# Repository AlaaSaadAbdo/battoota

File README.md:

# Disclaimer: Please keep in mind that there are prototypes here. Use the files at your own risk.

# Pictures

## Credits/references

All of the boards here wouldn't be possible without the help of some awesome people and their projects:
- [bredfield](https://github.com/bredfield)
- [Rae Dux](https://github.com/andrewjrae/rae-dux)
- [Rufous/Berylline](https://github.com/jcmkk3/trochilidae)
- [Sadek Baroudi](https://github.com/sadekbaroudi) of [fingerpunch](https://fingerpunch.xyz)
- [Hazel](https://github.com/jasonhazel)
- [Freznel](https://github.com/freznel10)
- [Duckyb](https://github.com/duckyb)
- [Grinnie](https://github.com/regicidalplutophage)
- [Weteor](https://github.com/weteor)
- [aki27](https://twitter.com/aki27kbd)
- [chewiedies](https://www.printables.com/@chewiedies_360738)

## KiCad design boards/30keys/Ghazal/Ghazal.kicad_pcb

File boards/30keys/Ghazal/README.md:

Ghazal is a wireless unibody.

Features:
- Integrated trackball using the PWM3610 via [VIK module](https://github.com/sadekbaroudi/vik/tree/master/pcb/pmw3610-xs)
- Display using nice!view
- Wireless using nice!nano

To build this board you'll need the following components after fabrication the board with PCBA

BOM:
- 1x nice!nano 
- 1x nice!view
- 1x battery I recommend a chunky one similar to LP785060
- XS-PMW3610 VIK module PCBA
- 34 MX/ChocV1 hotswap sockets
- 34 MX/CHocV1 switches
- Keycaps for the chose switches

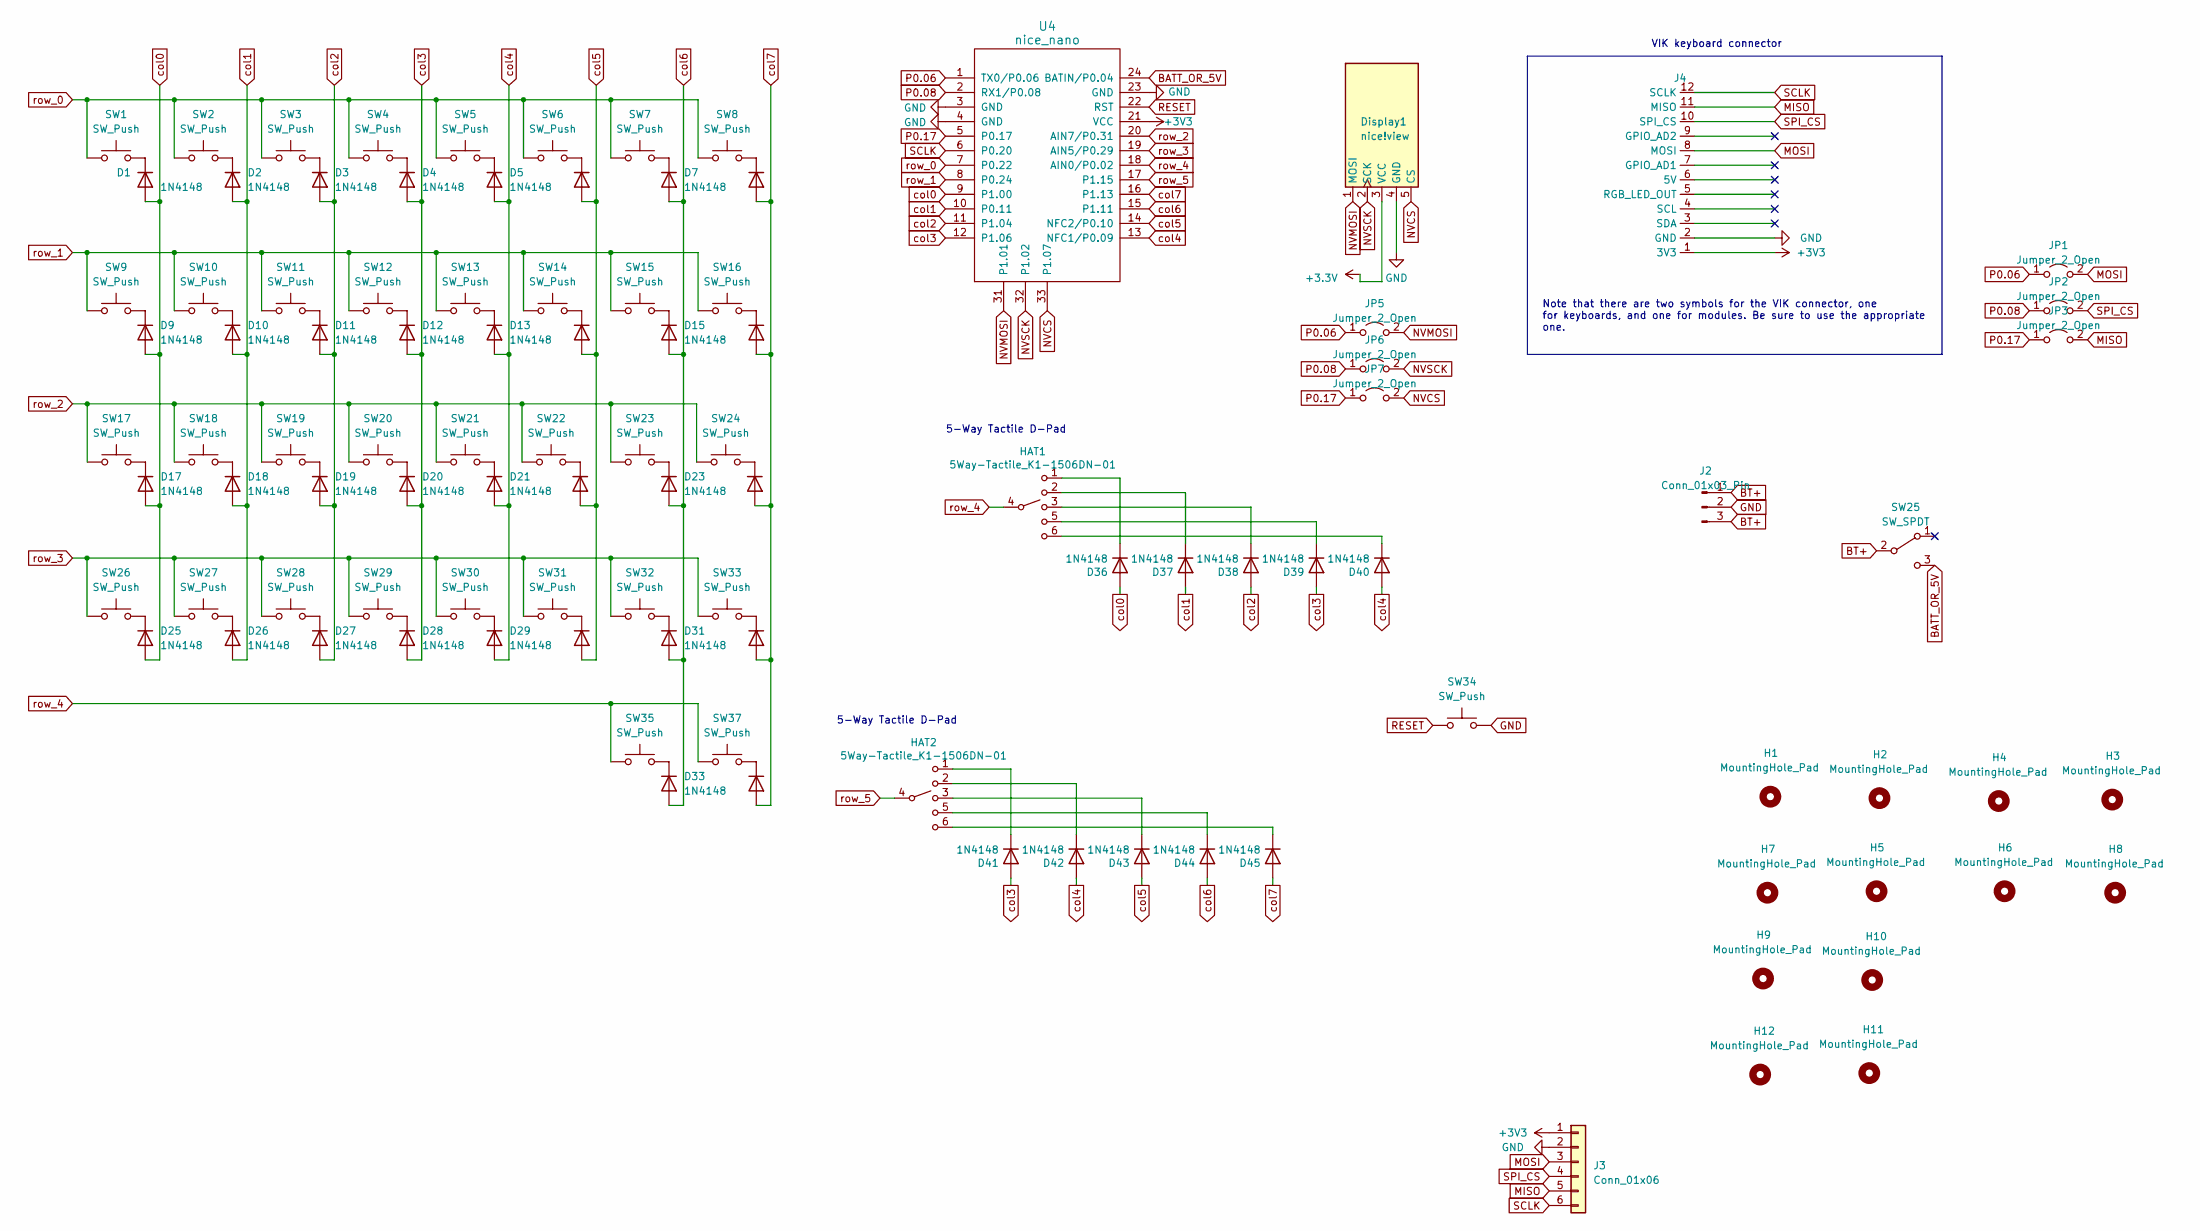
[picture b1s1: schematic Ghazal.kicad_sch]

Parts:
D1, D2, D3, D4, D5, D6, D7, D8, D9, D10, D11, D12, D13, D14, D15, D16, D17, D18, D19, D20, D21, D22, D23, D24, D25, D26, D27, D28, D29, D30, D31, D32, D33, D35, D36, D37, D38, D39, D40, D41, D42, D43, D44, D45: 1N4148; D_SOD-123; LCSC C8598
Display1: nice!view; nice_view
H1, H2, H3, H4, H5, H6, H7, H8, H9, H10, H11, H12: MountingHole_Pad; MountingHole_M3
HAT1, HAT2: 5Way-Tactile_K1-1506DN-01; 5Way-non-reverse
J2: Conn_01x03_Pin; 3JST_BAT
J3: Conn_01x06; PinHeader_1x06_P2.54mm_Vertical
J4: vik-keyboard-connector-horizontal; LCSC C479750
JP1, JP2, JP3, JP5, JP6, JP7: Jumper_2_Open; SolderJumper-2_P1.3mm_Open_TrianglePad1.0x1.5mm
SW1, SW2, SW3, SW4, SW5, SW6, SW7, SW8, SW9, SW10, SW11, SW12, SW13, SW14, SW15, SW16, SW17, SW18, SW19, SW20, SW21, SW22, SW23, SW24, SW26, SW27, SW28, SW29, SW30, SW31, SW32, SW33, SW35, SW37: SW_Push; Kailh_hotswap_only_MX-CHOC
SW25: SW_SPDT; SW_CuK_OS102011MA1QN1_SPDT_Angled
SW34: SW_Push; ResetSW
U4: nice_nano

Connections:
BATT_OR_5V: SW25.3 (C); also elsewhere on the board
BT+: J2.1, J2.3, SW25.2 (B)
GND: Display1.4 (GND), J2.2, J3.2, SW34.2; also elsewhere on the board
MISO: J3.5, JP3.2 (B); also elsewhere on the board
MOSI: J3.3, JP1.2 (B); also elsewhere on the board
NVCS: Display1.5 (CS), JP7.2 (B); also elsewhere on the board
NVMOSI: Display1.1 (MOSI), JP5.2 (B); also elsewhere on the board
NVSCK: Display1.2 (SCK), JP6.2 (B); also elsewhere on the board
unnamed: D1.1 (K), SW1.2
unnamed: D2.1 (K), SW2.2
unnamed: D3.1 (K), SW3.2
unnamed: D4.1 (K), SW4.2
unnamed: D5.1 (K), SW5.2
unnamed: D6.1 (K), SW6.2
unnamed: D7.1 (K), SW7.2
unnamed: D8.1 (K), SW8.2
unnamed: D9.1 (K), SW9.2
unnamed: D10.1 (K), SW10.2
unnamed: D11.1 (K), SW11.2
unnamed: D12.1 (K), SW12.2
unnamed: D13.1 (K), SW13.2
unnamed: D14.1 (K), SW14.2
unnamed: D15.1 (K), SW15.2
unnamed: D16.1 (K), SW16.2
unnamed: D17.1 (K), SW17.2
unnamed: D18.1 (K), SW18.2
unnamed: D19.1 (K), SW19.2
unnamed: D20.1 (K), SW20.2
unnamed: D21.1 (K), SW21.2
unnamed: D22.1 (K), SW22.2
unnamed: D23.1 (K), SW23.2
unnamed: D24.1 (K), SW24.2
unnamed: D25.1 (K), SW26.2
unnamed: D26.1 (K), SW27.2
unnamed: D27.1 (K), SW28.2
unnamed: D28.1 (K), SW29.2
unnamed: D29.1 (K), SW30.2
unnamed: D30.1 (K), SW31.2
unnamed: D31.1 (K), SW32.2
unnamed: D32.1 (K), SW33.2
unnamed: D33.1 (K), SW35.2
unnamed: D35.1 (K), SW37.2
unnamed: D36.1 (K), HAT1.1
unnamed: D37.1 (K), HAT1.2
unnamed: D38.1 (K), HAT1.3
unnamed: D39.1 (K), HAT1.5
unnamed: D40.1 (K), HAT1.6
unnamed: D41.1 (K), HAT2.1
unnamed: D42.1 (K), HAT2.2
unnamed: D43.1 (K), HAT2.3
unnamed: D44.1 (K), HAT2.5
unnamed: D45.1 (K), HAT2.6
P0.06: JP1.1 (A), JP5.1 (A); also elsewhere on the board
P0.08: JP2.1 (A), JP6.1 (A); also elsewhere on the board
P0.17: JP3.1 (A), JP7.1 (A); also elsewhere on the board
RESET: SW34.1; also elsewhere on the board
SCLK: J3.6; also elsewhere on the board
SPI_CS: J3.4, JP2.2 (B); also elsewhere on the board
col0: D1.2 (A), D9.2 (A), D17.2 (A), D25.2 (A), D36.2 (A); also elsewhere on the board
col1: D2.2 (A), D10.2 (A), D18.2 (A), D26.2 (A), D37.2 (A); also elsewhere on the board
col2: D3.2 (A), D11.2 (A), D19.2 (A), D27.2 (A), D38.2 (A); also elsewhere on the board
col3: D4.2 (A), D12.2 (A), D20.2 (A), D28.2 (A), D39.2 (A), D41.2 (A); also elsewhere on the board
col4: D5.2 (A), D13.2 (A), D21.2 (A), D29.2 (A), D40.2 (A), D42.2 (A); also elsewhere on the board
col5: D6.2 (A), D14.2 (A), D22.2 (A), D30.2 (A), D43.2 (A); also elsewhere on the board
col6: D7.2 (A), D15.2 (A), D23.2 (A), D31.2 (A), D33.2 (A), D44.2 (A); also elsewhere on the board
col7: D8.2 (A), D16.2 (A), D24.2 (A), D32.2 (A), D35.2 (A), D45.2 (A); also elsewhere on the board
row_0: SW1.1, SW2.1, SW3.1, SW4.1, SW5.1, SW6.1, SW7.1, SW8.1; also elsewhere on the board
row_1: SW9.1, SW10.1, SW11.1, SW12.1, SW13.1, SW14.1, SW15.1, SW16.1; also elsewhere on the board
row_2: SW17.1, SW18.1, SW19.1, SW20.1, SW21.1, SW22.1, SW23.1, SW24.1; also elsewhere on the board
row_3: SW26.1, SW27.1, SW28.1, SW29.1, SW30.1, SW31.1, SW32.1, SW33.1; also elsewhere on the board
row_4: HAT1.4, SW35.1, SW37.1; also elsewhere on the board
row_5: HAT2.4; also elsewhere on the board

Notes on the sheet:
Note that there are two symbols for the VIK connector, one for keyboards, and one for modules. Be sure to use the appropriate one.
5-Way Tactile D-Pad
VIK keyboard connector

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
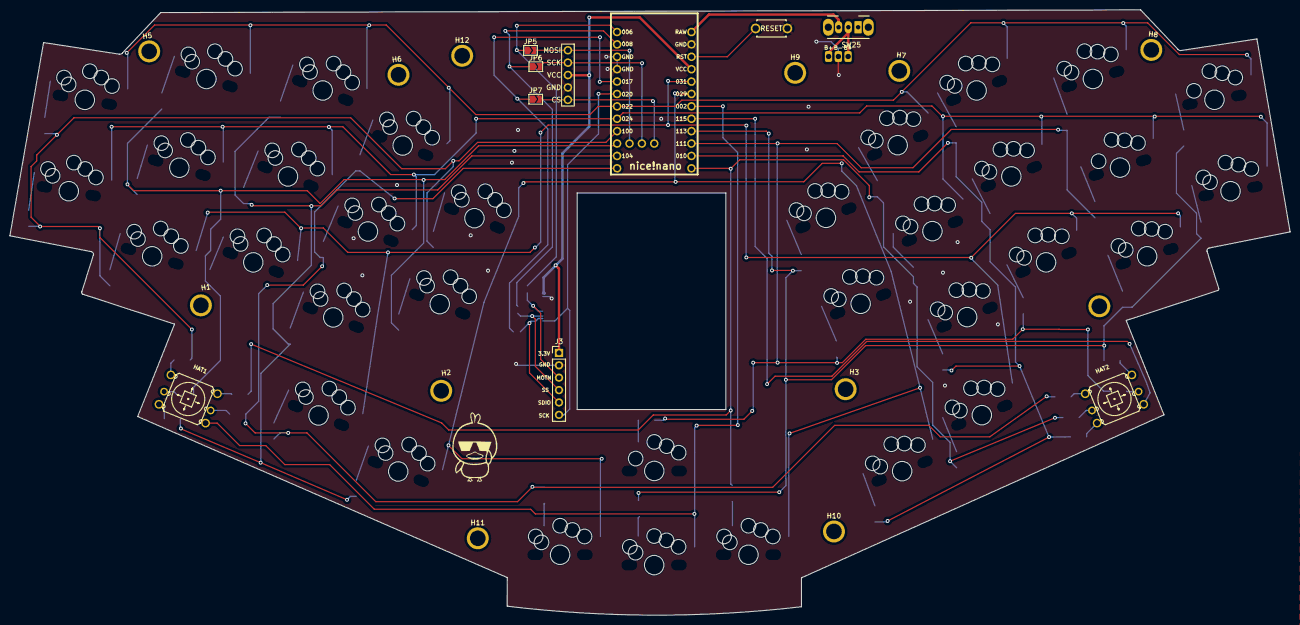
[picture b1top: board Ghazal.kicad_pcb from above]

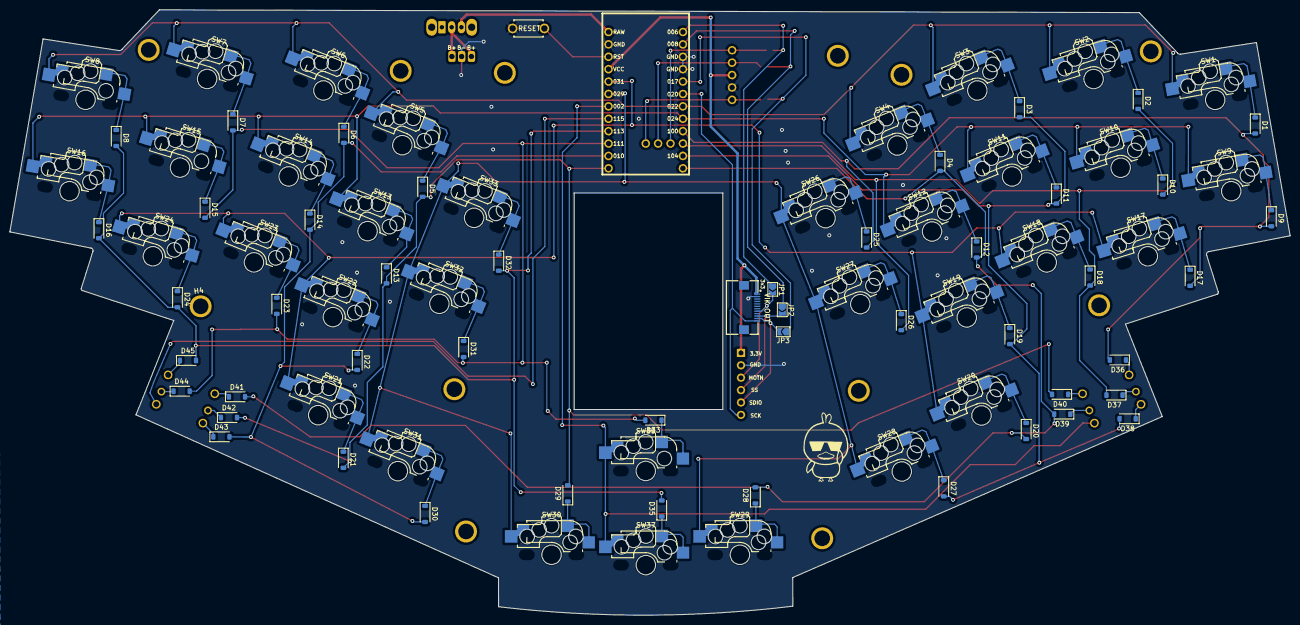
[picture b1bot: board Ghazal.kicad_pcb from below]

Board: 2 copper layers, 262.4 x 124.1 mm, 105 parts (48 on the bottom side), 73 nets.

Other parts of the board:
J1: vik-keyboard-connector-horizontal
U1: nice_nano

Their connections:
BATT_OR_5V: U1.24 (BATIN/P0.04); also elsewhere on the board
GND: J1.2 (GND), U1.3 (GND), U1.4 (GND), U1.23 (GND); also elsewhere on the board
MISO: J1.11 (MISO); also elsewhere on the board
MOSI: J1.8 (MOSI); also elsewhere on the board
NVCS: U1.33 (P1.07); also elsewhere on the board
NVMOSI: U1.31 (P1.01); also elsewhere on the board
NVSCK: U1.32 (P1.02); also elsewhere on the board
P0.06: U1.1 (TX0/P0.06); also elsewhere on the board
P0.08: U1.2 (RX1/P0.08); also elsewhere on the board
P0.17: U1.5 (P0.17); also elsewhere on the board
RESET: U1.22 (RST); also elsewhere on the board
SCLK: J1.12 (SCLK), U1.6 (P0.20); also elsewhere on the board
SPI_CS: J1.10 (SPI_CS); also elsewhere on the board
col0: U1.9 (P1.00); also elsewhere on the board
col1: U1.10 (P0.11); also elsewhere on the board
col2: U1.11 (P1.04); also elsewhere on the board
col3: U1.12 (P1.06); also elsewhere on the board
col4: U1.13 (NFC1/P0.09); also elsewhere on the board
col5: U1.14 (NFC2/P0.10); also elsewhere on the board
col6: U1.15 (P1.11); also elsewhere on the board
col7: U1.16 (P1.13); also elsewhere on the board
row_0: U1.7 (P0.22); also elsewhere on the board
row_1: U1.8 (P0.24); also elsewhere on the board
row_2: U1.20 (AIN7/P0.31); also elsewhere on the board
row_3: U1.19 (AIN5/P0.29); also elsewhere on the board
row_4: U1.18 (AIN0/P0.02); also elsewhere on the board
row_5: U1.17 (P1.15); also elsewhere on the board

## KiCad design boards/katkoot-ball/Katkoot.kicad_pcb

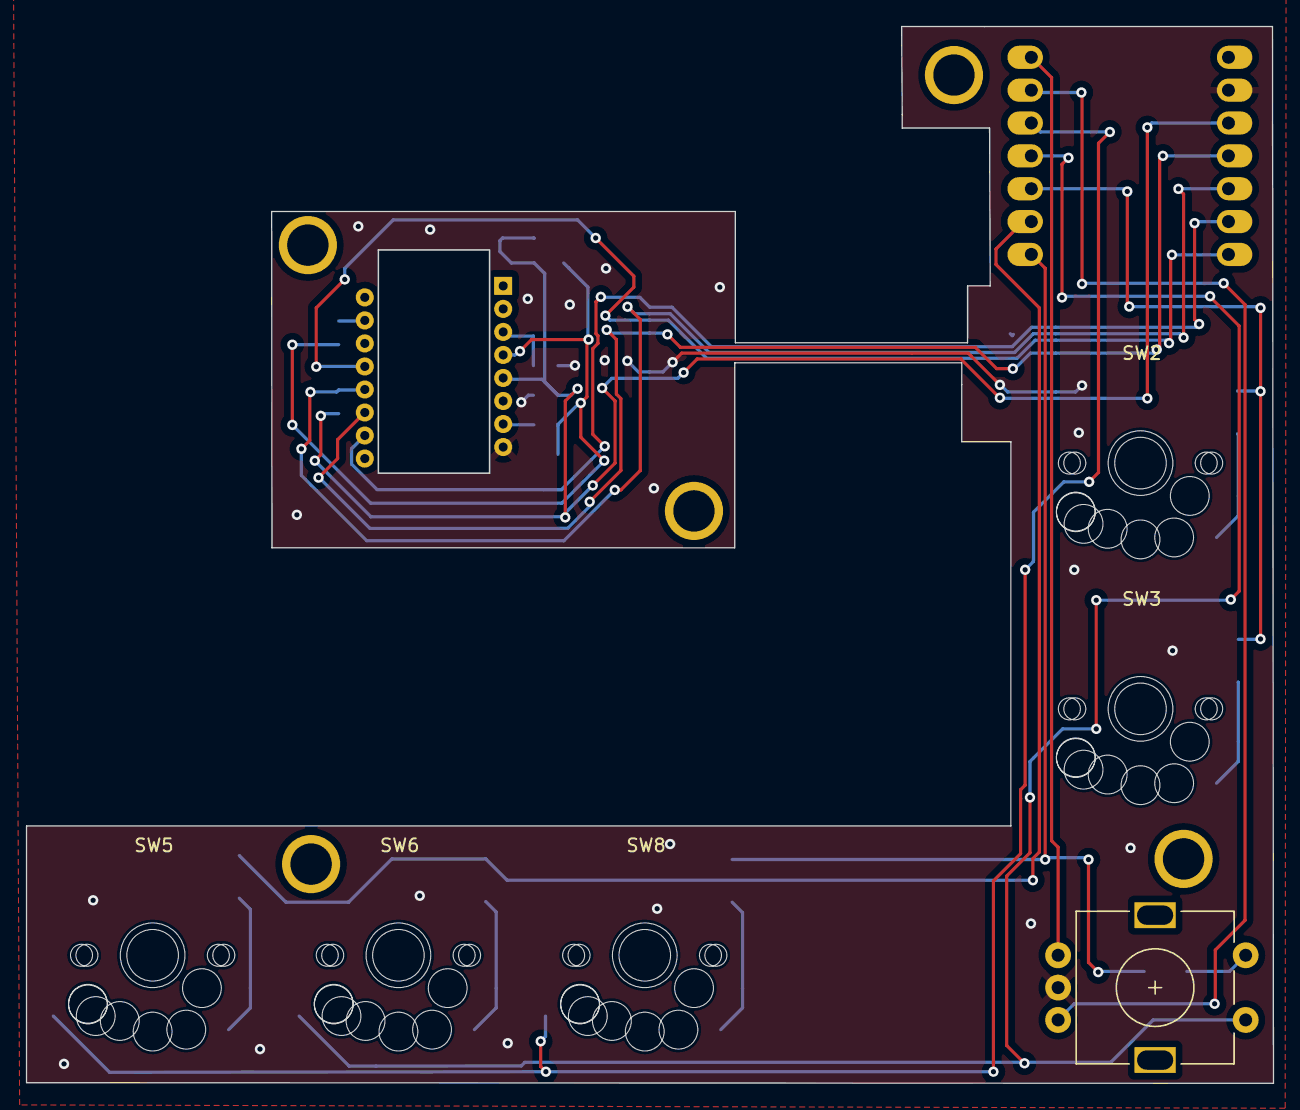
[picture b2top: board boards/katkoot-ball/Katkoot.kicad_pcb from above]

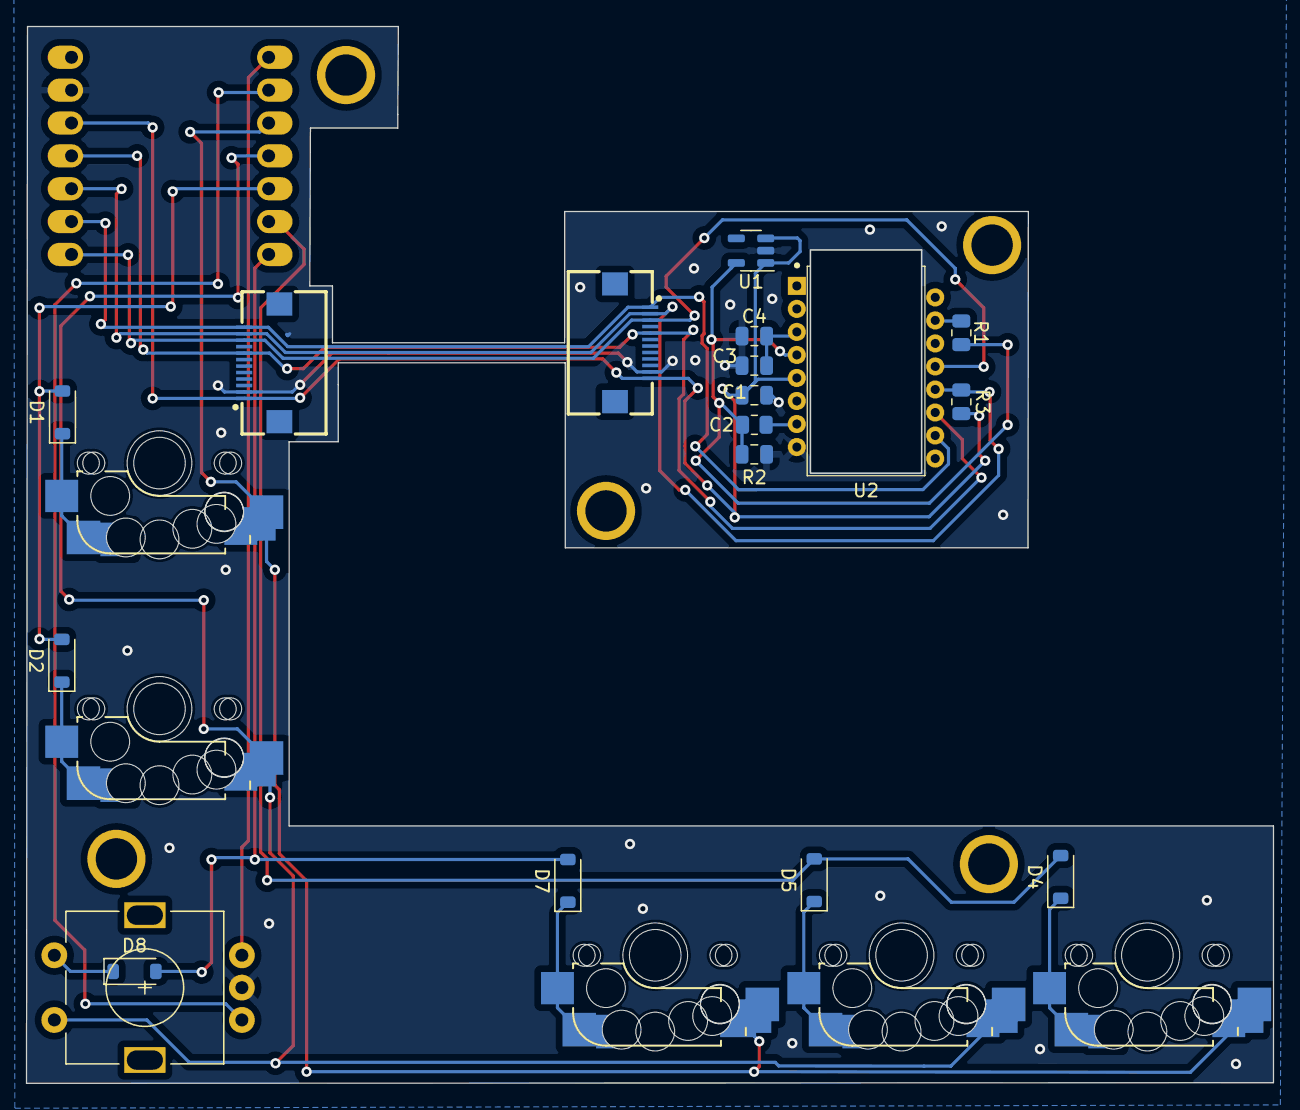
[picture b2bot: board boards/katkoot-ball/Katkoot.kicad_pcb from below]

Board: 2 copper layers, 96.4 x 81.7 mm, 24 parts (17 on the bottom side), 23 nets.

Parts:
C1, C4: 0.1uF; C_0805_2012Metric
C2: 1uF; C_0805_2012Metric
C3: 4.7uF; C_0805_2012Metric
D1, D2, D4, D5, D7, D8: 1N4148; D_SOD-123
J1, J2: FPC-SMD_FPC05012-09200-.5mm-rev
R1: 39; R_0805_2012Metric
R2, R3: 10K; R_0805_2012Metric
SW1: Rotary_Encoder_Switch; RotaryEncoder_Alps_EC11E-Switch_Vertical_H20mm-keebio_modif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
SW2, SW3, SW5, SW6, SW8: SW_Push; gateron-ks27-choc-v1-mx-hotswap
U1: TCR2EF19,LM(CT; SOT-23-5
U2: PMW3360DM-T2QU
U3: xiao-ble; xiao-ble-smd-cutout

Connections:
ENC_L: SW1.A, U3.1 (A2/0.02_H)
ENC_R: SW1.B, U3.2 (A4/0.03_H)
GND: C1.2, C2.2, C3.2, C4.1, J1.2 (GND), J2.11 (GND), SW1.C, U1.2 (GND), U2.8 (GND), U3.13 (GND)
MISO: J1.11 (MISO), J2.2 (MISO), R3.1, U2.12 (MISO), U3.10 (A5_MISO/1.14)
MOSI: J1.8 (MOSI), J2.5 (MOSI), U2.11 (MOSI), U3.11 (A6_MOSI/1.15)
NCS: J1.10 (SPI_CS), J2.3 (SPI_CS), U2.13 (~NCS), U3.8 (B9_RX/1.12)
unnamed: D1.1 (K), SW2.2
unnamed: D2.1 (K), SW3.2
unnamed: D4.1 (K), SW5.2
unnamed: D5.1 (K), SW6.2
unnamed: D7.1 (K), SW8.2
unnamed: D8.1 (K), SW1.S2
unnamed: R1.2, U2.15 (LED_P)
unnamed: C3.1, C4.2, U2.3 (VDDPIX)
unnamed: R2.1, U2.7 (~NRESET)
SCLK: J1.12 (SCLK), J2.1 (SCLK), U2.10 (SCLK), U3.9 (A7_SCK/1.13)
VCC: C1.1, J1.1 (3V3), J2.12 (3V3), R3.2, U1.1 (IN), U1.3 (EN), U2.5 (VDDIO), U3.12 (3V3)
VDD: C2.1, R1.1, R2.2, U1.5 (OUT), U2.4 (VDD)
col0: D1.2 (A), D2.2 (A), U3.5 (A8_SDA/0.04_H)
col1: D4.2 (A), D5.2 (A), U3.6 (A9_SCL/0.05_H)
col2: D7.2 (A), D8.2 (A), U3.7 (B8_TX/1.11)
row_0: SW2.1, SW5.1, SW8.1, U3.3 (A10/0.28)
row_1: SW1.S1, SW3.1, SW6.1, U3.4 (A11/0.29)

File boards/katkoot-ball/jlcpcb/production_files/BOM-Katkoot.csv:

Comment,Designator,Footprint,LCSC
~,"J1,J2",FPC-SMD_FPC05012-09200-.5mm-rev,C2911838
4.7uF,C3,C_0805_2012Metric,C303940
10K,"R2,R3",R_0805_2012Metric,C406725
39,R1,R_0805_2012Metric,C514993
1uF,C2,C_0805_2012Metric,C519973
"TCR2EF19,LM(CT",U1,SOT-23-5,C697975
0.1uF,"C1,C4",C_0805_2012Metric,C77456
1N4148,"D1,D2,D4,D5,D7,D8",D_SOD-123,C8598

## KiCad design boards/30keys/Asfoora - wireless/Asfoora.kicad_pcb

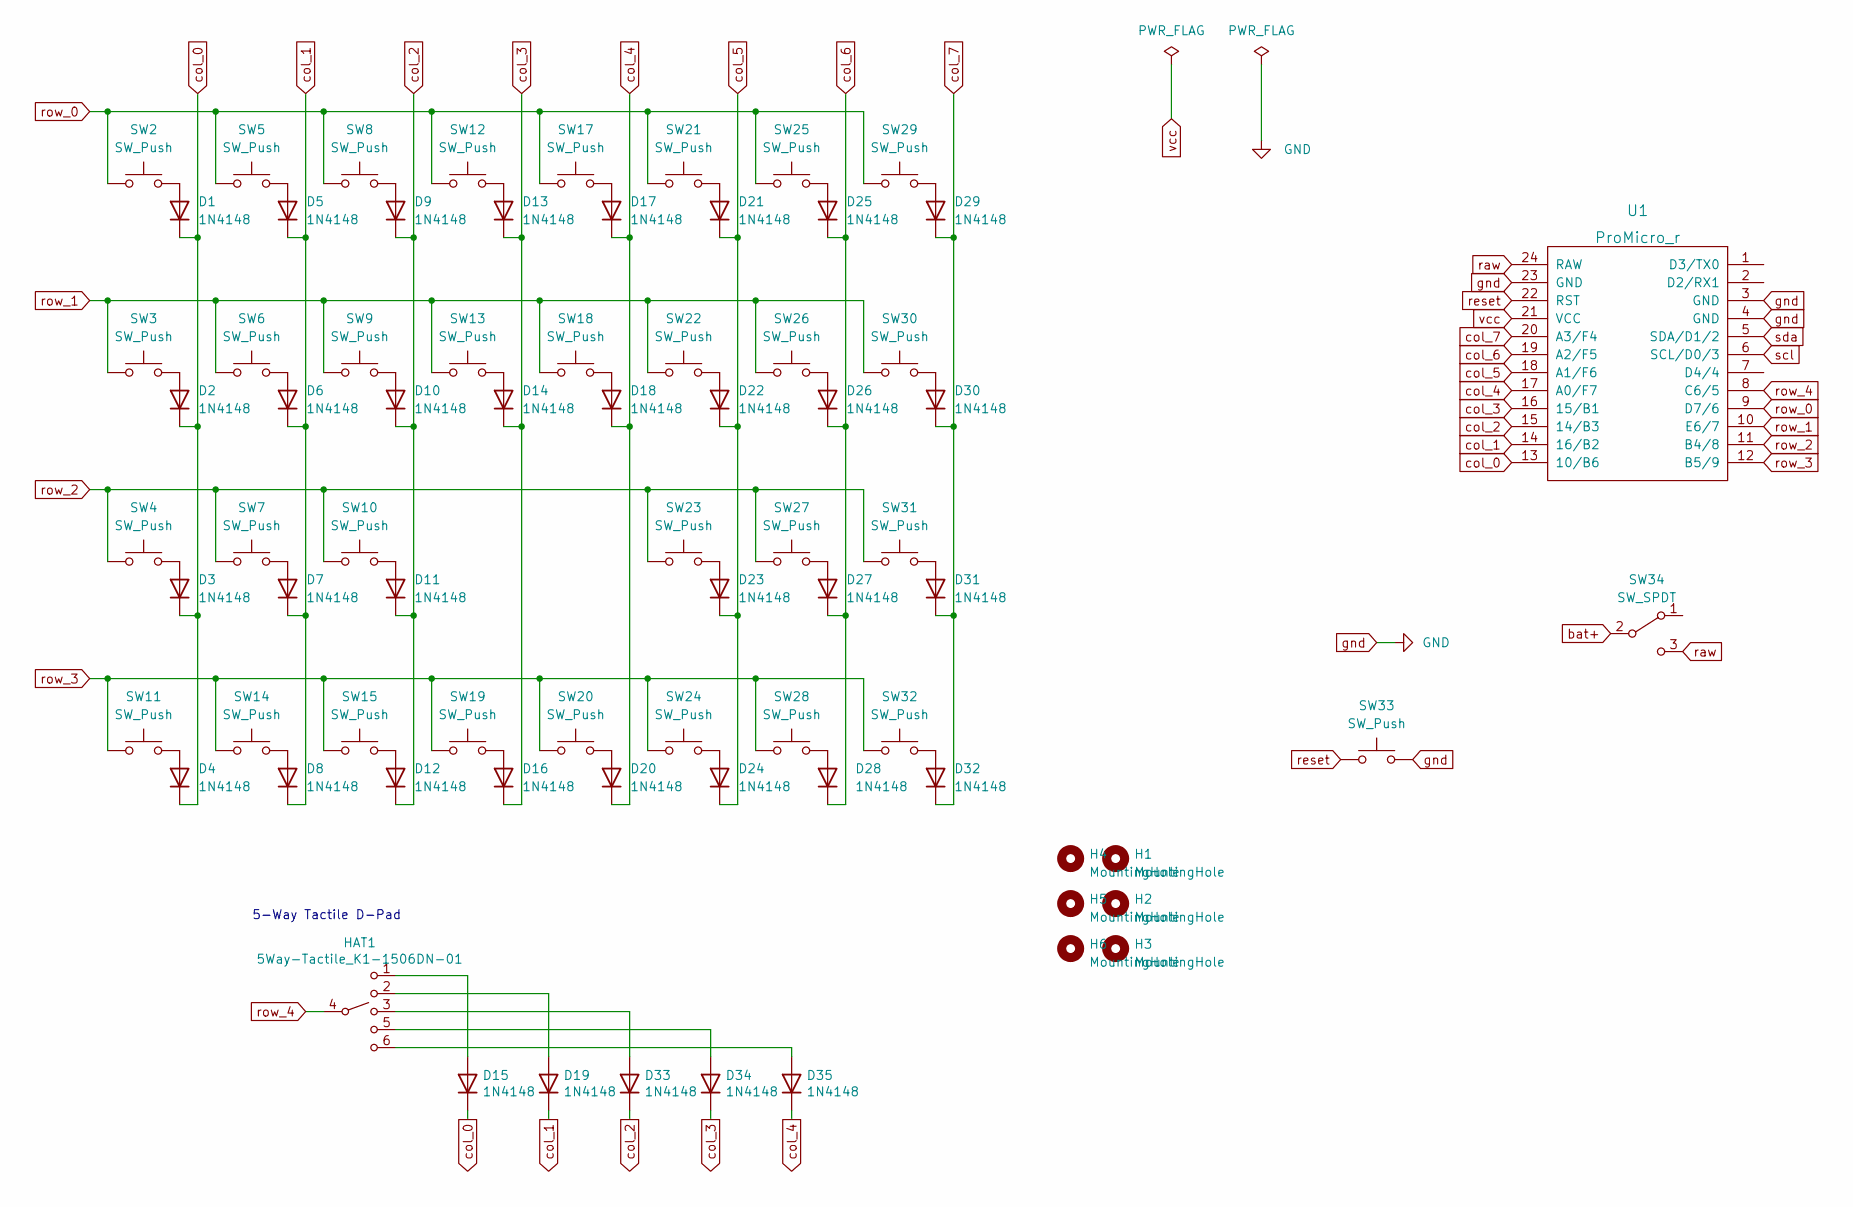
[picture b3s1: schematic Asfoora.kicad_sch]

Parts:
D1, D2, D3, D4, D5, D6, D7, D8, D9, D10, D11, D12, D13, D14, D15, D16, D17, D18, D19, D20, D21, D22, D23, D24, D25, D26, D27, D28, D29, D30, D31, D32, D33, D34, D35: 1N4148; D_SOD-123; LCSC C909967
H1, H2, H3, H4, H5, H6: MountingHole; MountingHole_M3
HAT1: 5Way-Tactile_K1-1506DN-01; 5Way-non-reverse
SW2, SW3, SW4, SW5, SW6, SW7, SW8, SW9, SW10, SW11, SW12, SW13, SW14, SW15, SW17, SW18, SW19, SW20, SW21, SW22, SW23, SW24, SW25, SW26, SW27, SW28, SW29, SW30, SW31, SW32: SW_Push; Kailh_hotswap_MX-CHOC
SW33: SW_Push; ResetSW
SW34: SW_SPDT; SW_CuK_OS102011MA1QN1_SPDT_Angled
U1: ProMicro_r; ProMicro_v3.5

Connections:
unnamed: D1.2 (A), SW2.2
unnamed: D2.2 (A), SW3.2
unnamed: D3.2 (A), SW4.2
unnamed: D4.2 (A), SW11.2
unnamed: D5.2 (A), SW5.2
unnamed: D6.2 (A), SW6.2
unnamed: D7.2 (A), SW7.2
unnamed: D8.2 (A), SW14.2
unnamed: D9.2 (A), SW8.2
unnamed: D10.2 (A), SW9.2
unnamed: D11.2 (A), SW10.2
unnamed: D12.2 (A), SW15.2
unnamed: D13.2 (A), SW12.2
unnamed: D14.2 (A), SW13.2
unnamed: D15.2 (A), HAT1.1
unnamed: D16.2 (A), SW19.2
unnamed: D17.2 (A), SW17.2
unnamed: D18.2 (A), SW18.2
unnamed: D19.2 (A), HAT1.2
unnamed: D20.2 (A), SW20.2
unnamed: D21.2 (A), SW21.2
unnamed: D22.2 (A), SW22.2
unnamed: D23.2 (A), SW23.2
unnamed: D24.2 (A), SW24.2
unnamed: D25.2 (A), SW25.2
unnamed: D26.2 (A), SW26.2
unnamed: D27.2 (A), SW27.2
unnamed: D28.2 (A), SW28.2
unnamed: D29.2 (A), SW29.2
unnamed: D30.2 (A), SW30.2
unnamed: D31.2 (A), SW31.2
unnamed: D32.2 (A), SW32.2
unnamed: D33.2 (A), HAT1.3
unnamed: D34.2 (A), HAT1.5
unnamed: D35.2 (A), HAT1.6
bat+: SW34.2 (B); also elsewhere on the board
col_0: D1.1 (K), D2.1 (K), D3.1 (K), D4.1 (K), D15.1 (K), U1.13 (10/B6)
col_1: D5.1 (K), D6.1 (K), D7.1 (K), D8.1 (K), D19.1 (K), U1.14 (16/B2)
col_2: D9.1 (K), D10.1 (K), D11.1 (K), D12.1 (K), D33.1 (K), U1.15 (14/B3)
col_3: D13.1 (K), D14.1 (K), D16.1 (K), D34.1 (K), U1.16 (15/B1)
col_4: D17.1 (K), D18.1 (K), D20.1 (K), D35.1 (K), U1.17 (A0/F7)
col_5: D21.1 (K), D22.1 (K), D23.1 (K), D24.1 (K), U1.18 (A1/F6)
col_6: D25.1 (K), D26.1 (K), D27.1 (K), D28.1 (K), U1.19 (A2/F5)
col_7: D29.1 (K), D30.1 (K), D31.1 (K), D32.1 (K), U1.20 (A3/F4)
gnd: SW33.2, U1.3 (GND), U1.4 (GND), U1.23 (GND); also elsewhere on the board
raw: SW34.3 (C), U1.24 (RAW)
reset: SW33.1, U1.22 (RST)
row_0: SW2.1, SW5.1, SW8.1, SW12.1, SW17.1, SW21.1, SW25.1, SW29.1, U1.9 (D7/6)
row_1: SW3.1, SW6.1, SW9.1, SW13.1, SW18.1, SW22.1, SW26.1, SW30.1, U1.10 (E6/7)
row_2: SW4.1, SW7.1, SW10.1, SW23.1, SW27.1, SW31.1, U1.11 (B4/8)
row_3: SW11.1, SW14.1, SW15.1, SW19.1, SW20.1, SW24.1, SW28.1, SW32.1, U1.12 (B5/9)
row_4: HAT1.4, U1.8 (C6/5)
scl: U1.6 (SCL/D0/3)
sda: U1.5 (SDA/D1/2)
vcc: U1.21 (VCC)

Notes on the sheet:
5-Way Tactile D-Pad

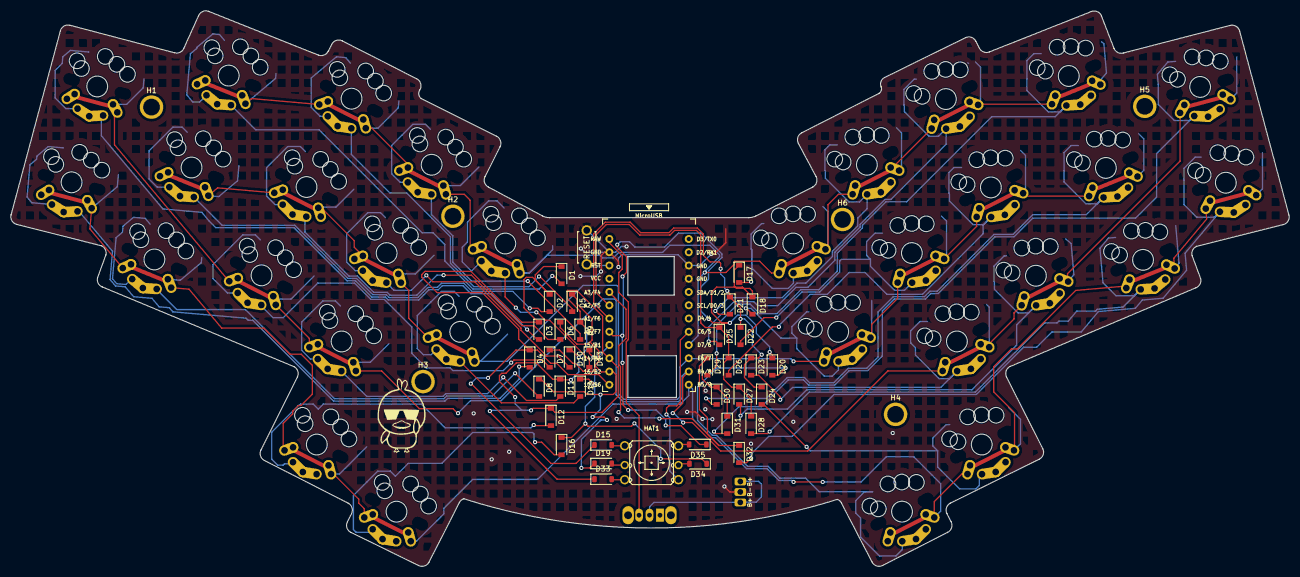
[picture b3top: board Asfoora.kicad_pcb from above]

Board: 2 copper layers, 245.0 x 106.5 mm, 76 parts (1 on the bottom side), 52 nets.

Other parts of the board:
PAD1: bat

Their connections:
bat+: PAD1.1, PAD1.3; also elsewhere on the board
gnd: PAD1.2; also elsewhere on the board

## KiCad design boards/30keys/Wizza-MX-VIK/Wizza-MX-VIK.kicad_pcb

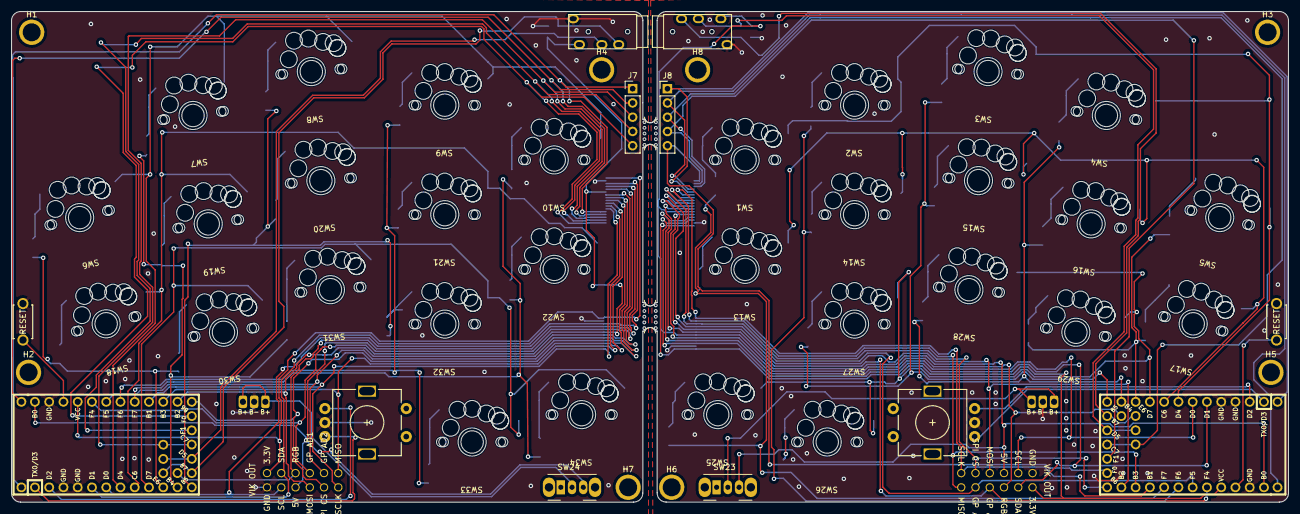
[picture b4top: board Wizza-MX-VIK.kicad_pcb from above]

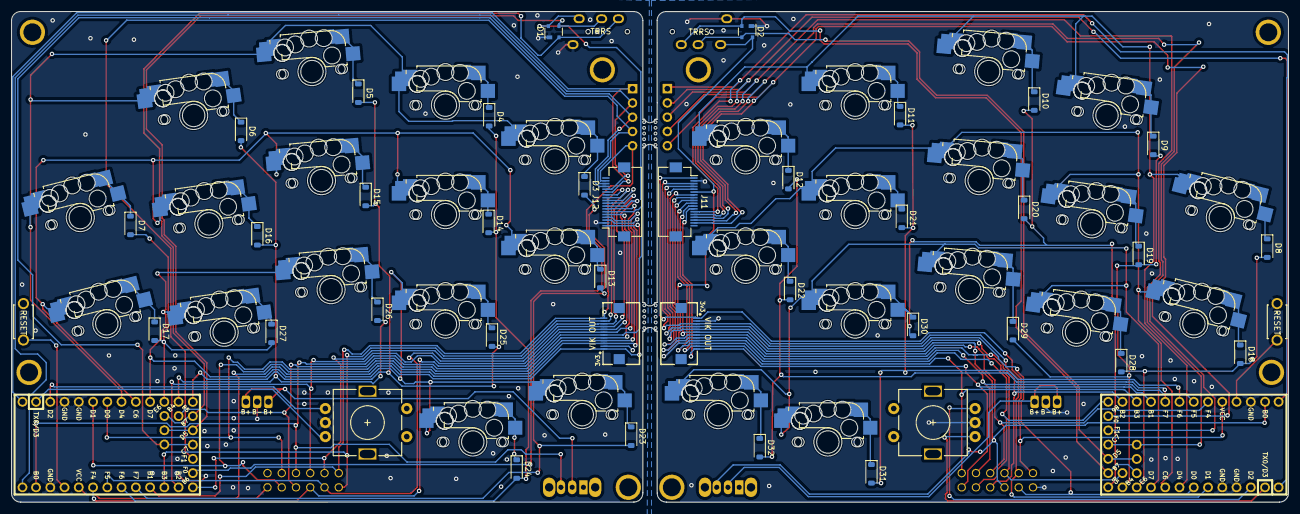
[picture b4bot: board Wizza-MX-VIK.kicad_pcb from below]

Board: 2 copper layers, 227.5 x 87.4 mm, 92 parts (36 on the bottom side), 92 nets.

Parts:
D1, D2: PRTR5V0U2X; SOT-143
D3, D4, D5, D6, D7, D8, D9, D10, D11, D12, D13, D14, D15, D16, D17, D18, D19, D20, D21, D22, D23, D24, D25, D26, D27, D28, D29, D30, D31, D32: 1N4148; D_SOD-123
H1, H2, H3, H4, H5, H6, H7, H8: MountingHole; MountingHole_M3
J1, J2: vik-keyboard-connector-horizontal
J3, J4: AudioJack4dpb; TRRS-PJ-320A
J5, J6: vik-keyboard-throughole
J7, J8: Conn_01x05; PinHeader_1x05_P2.54mm_Vertical
J9, J10: Conn_01x03_Socket; 3JST_BAT
J11, J12: Conn_01x18; FPC-SMD_FPC05018-09200-.5mm-rev
SW1, SW2, SW3, SW4, SW5, SW6, SW7, SW8, SW9, SW10, SW13, SW14, SW15, SW16, SW17, SW18, SW19, SW20, SW21, SW22, SW25, SW26, SW27, SW28, SW29, SW30, SW31, SW32, SW33, SW34: SW_Push; gateron-ks27-choc-v1-mx-hotswap
SW11, SW12: SW_Push; ResetSW
SW23, SW24: SW_SPDT; SW_CuK_OS102011MA1QN1_SPDT_Angled
SW35, SW36: Rotary_Encoder_Switch; RotaryEncoder_Alps_EC11E-Switch_Vertical_H20mm-keebio_modif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
U1, U2: Helios; Helios-Nano
mouse-bite-2mm-slot, mouse-bite-2mm-slot#2: VAL**; mouse-bite-5mm-slot-with-space-for-track

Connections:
BAT_L: J9.1, J9.3, SW24.2 (B)
BAT_R: J10.1, J10.3, SW23.2 (B)
EncL_L: SW35.A, U2.2 (RX1/PD2)
EncL_R: SW36.B, U1.2 (RX1/PD2)
EncR_L: SW35.B, U2.1 (TX0/PD3)
EncR_R: SW36.A, U1.1 (TX0/PD3)
GND_L: D2.1 (GND), J2.2 (GND), J3.C, J6.2 (GND), J9.2, J11.2, SW12.2, SW35.C, U2.3 (GND), U2.4 (GND), U2.23 (GND)
GND_R: D1.1 (GND), J1.2 (GND), J4.C, J5.2 (GND), J10.2, J12.2, SW11.2, SW36.C, U1.3 (GND), U1.4 (GND), U1.23 (GND)
GPIO10_L: J7.1, J11.13, U2.31 (GPIO10)
GPIO10_R: J8.1, J12.13, U1.31 (GPIO10)
GPIO11_L: J7.2, J11.14, U2.32 (GPIO11)
GPIO11_R: J8.2, J12.14, U1.32 (GPIO11)
GPIO14_L: J7.3, J11.15, U2.27 (C7)
GPIO14_R: J8.3, J12.15, U1.27 (C7)
GPIO15_L: J7.4, J11.16, U2.28 (F1)
GPIO15_R: J8.4, J12.16, U1.28 (F1)
GPIO16_L: J7.5, J11.17, U2.29 (F0)
GPIO16_R: J8.5, J12.17, U1.29 (F0)
LED_5V_L: J2.5 (RGB_LED_OUT), J6.5 (RGB_LED_OUT), J11.5, U2.30 (RGB)
LED_5V_R: J1.5 (RGB_LED_OUT), J5.5 (RGB_LED_OUT), J12.5, U1.30 (RGB)
MISO_L: J2.11 (MISO), J6.11 (MISO), J11.11, U2.15 (14/PB3)
MISO_R: J1.11 (MISO), J5.11 (MISO), J12.11, U1.15 (14/PB3)
MOSI_L: J2.8 (MOSI), J6.8 (MOSI), J11.8, U2.14 (16/PB2)
MOSI_R: J1.8 (MOSI), J5.8 (MOSI), J12.8, U1.14 (16/PB2)
NCS_L: J2.10 (SPI_CS), J6.10 (SPI_CS), J11.10, U2.13 (10/PB6)
NCS_R: J1.10 (SPI_CS), J5.10 (SPI_CS), J12.10, U1.13 (10/PB6)
unnamed: D3.1 (K), SW1.2
unnamed: D4.1 (K), SW2.2
unnamed: D5.1 (K), SW3.2
unnamed: D6.1 (K), SW4.2
unnamed: D7.1 (K), SW5.2
unnamed: D8.1 (K), SW6.2
unnamed: D9.1 (K), SW7.2
unnamed: D10.1 (K), SW8.2
unnamed: D11.1 (K), SW9.2
unnamed: D12.1 (K), SW10.2
unnamed: D13.1 (K), SW13.2
unnamed: D14.1 (K), SW14.2
unnamed: D15.1 (K), SW15.2
unnamed: D16.1 (K), SW16.2
unnamed: D17.1 (K), SW17.2
unnamed: D18.1 (K), SW18.2
unnamed: D19.1 (K), SW19.2
unnamed: D20.1 (K), SW20.2
unnamed: D21.1 (K), SW21.2
unnamed: D22.1 (K), SW22.2
unnamed: D23.1 (K), SW25.2
unnamed: D24.1 (K), SW26.2
unnamed: D25.1 (K), SW27.2
unnamed: D26.1 (K), SW28.2
unnamed: D27.1 (K), SW29.2
unnamed: D28.1 (K), SW30.2
unnamed: D29.1 (K), SW31.2
unnamed: D30.1 (K), SW32.2
unnamed: D31.1 (K), SW33.2
unnamed: D32.1 (K), SW34.2
RAW_L: D2.4 (VCC), J2.6 (5V), J3.D, J6.6 (5V), J11.6, SW24.3 (C), U2.24 (B0)
RAW_R: D1.4 (VCC), J1.6 (5V), J4.D, J5.6 (5V), J12.6, SW23.3 (C), U1.24 (B0)
RESET_L: SW12.1, U2.22 (RST)
RESET_R: SW11.1, U1.22 (RST)
RX_L: D2.3 (I/O2), J3.A, U2.26 (D5)
RX_R: D1.3 (I/O2), J4.A, U1.26 (D5)
SCLK_L: J2.12 (SCLK), J6.12 (SCLK), J11.12, U2.16 (15/PB1)
SCLK_R: J1.12 (SCLK), J5.12 (SCLK), J12.12, U1.16 (15/PB1)
SCL_L: J2.4 (SCL), J6.4 (SCL), J11.4, U2.6 (3/PD0)
SCL_R: J1.4 (SCL), J5.4 (SCL), J12.4, U1.6 (3/PD0)
SDA_L: J2.3 (SDA), J6.3 (SDA), J11.3, U2.5 (2/PD1)
SDA_R: J1.3 (SDA), J5.3 (SDA), J12.3, U1.5 (2/PD1)
TX_L: D2.2 (I/O1), J3.B, U2.25 (B7)
TX_R: D1.2 (I/O1), J4.B, U1.25 (B7)
VCC_L: J2.1 (3V3), J6.1 (3V3), J11.1, U2.21 (VCC)
VCC_R: J1.1 (3V3), J5.1 (3V3), J12.1, U1.21 (VCC)
VIK_AD1_L: J2.7 (GPIO_AD1), J6.7 (GPIO_AD1), J11.7, U2.20 (A3/PF4)
VIK_AD1_R: J1.7 (GPIO_AD1), J5.7 (GPIO_AD1), J12.7, U1.20 (A3/PF4)
VIK_AD2_L: J2.9 (GPIO_AD2), J6.9 (GPIO_AD2), J11.9, U2.19 (A2/PF5)
VIK_AD2_R: J1.9 (GPIO_AD2), J5.9 (GPIO_AD2), J12.9, U1.19 (A2/PF5)
col0_L: D8.2 (A), D18.2 (A), D28.2 (A), U2.10 (7/PE6)
col0_R: D7.2 (A), D17.2 (A), D27.2 (A), U1.10 (7/PE6)
col1_L: D9.2 (A), D19.2 (A), D29.2 (A), U2.11 (8/PB4)
col1_R: D6.2 (A), D16.2 (A), D26.2 (A), U1.11 (8/PB4)
col2_L: D10.2 (A), D20.2 (A), D30.2 (A), U2.12 (9/PB5)
col2_R: D5.2 (A), D15.2 (A), D25.2 (A), U1.12 (9/PB5)
col3_L: D11.2 (A), D21.2 (A), D31.2 (A), U2.18 (A1/PF6)
col3_R: D4.2 (A), D14.2 (A), D24.2 (A), U1.18 (A1/PF6)
col4_L: D12.2 (A), D22.2 (A), D32.2 (A), U2.17 (A0/PF7)
col4_R: D3.2 (A), D13.2 (A), D23.2 (A), U1.17 (A0/PF7)
row_0_L: SW6.1, SW7.1, SW8.1, SW9.1, SW10.1, U2.7 (4/PD4)
row_0_R: SW1.1, SW2.1, SW3.1, SW4.1, SW5.1, U1.7 (4/PD4)
row_1_L: SW18.1, SW19.1, SW20.1, SW21.1, SW22.1, U2.8 (5/PC6)
row_1_R: SW13.1, SW14.1, SW15.1, SW16.1, SW17.1, U1.8 (5/PC6)
row_2_L: SW30.1, SW31.1, SW32.1, SW33.1, SW34.1, U2.9 (6/PD7)
row_2_R: SW25.1, SW26.1, SW27.1, SW28.1, SW29.1, U1.9 (6/PD7)
